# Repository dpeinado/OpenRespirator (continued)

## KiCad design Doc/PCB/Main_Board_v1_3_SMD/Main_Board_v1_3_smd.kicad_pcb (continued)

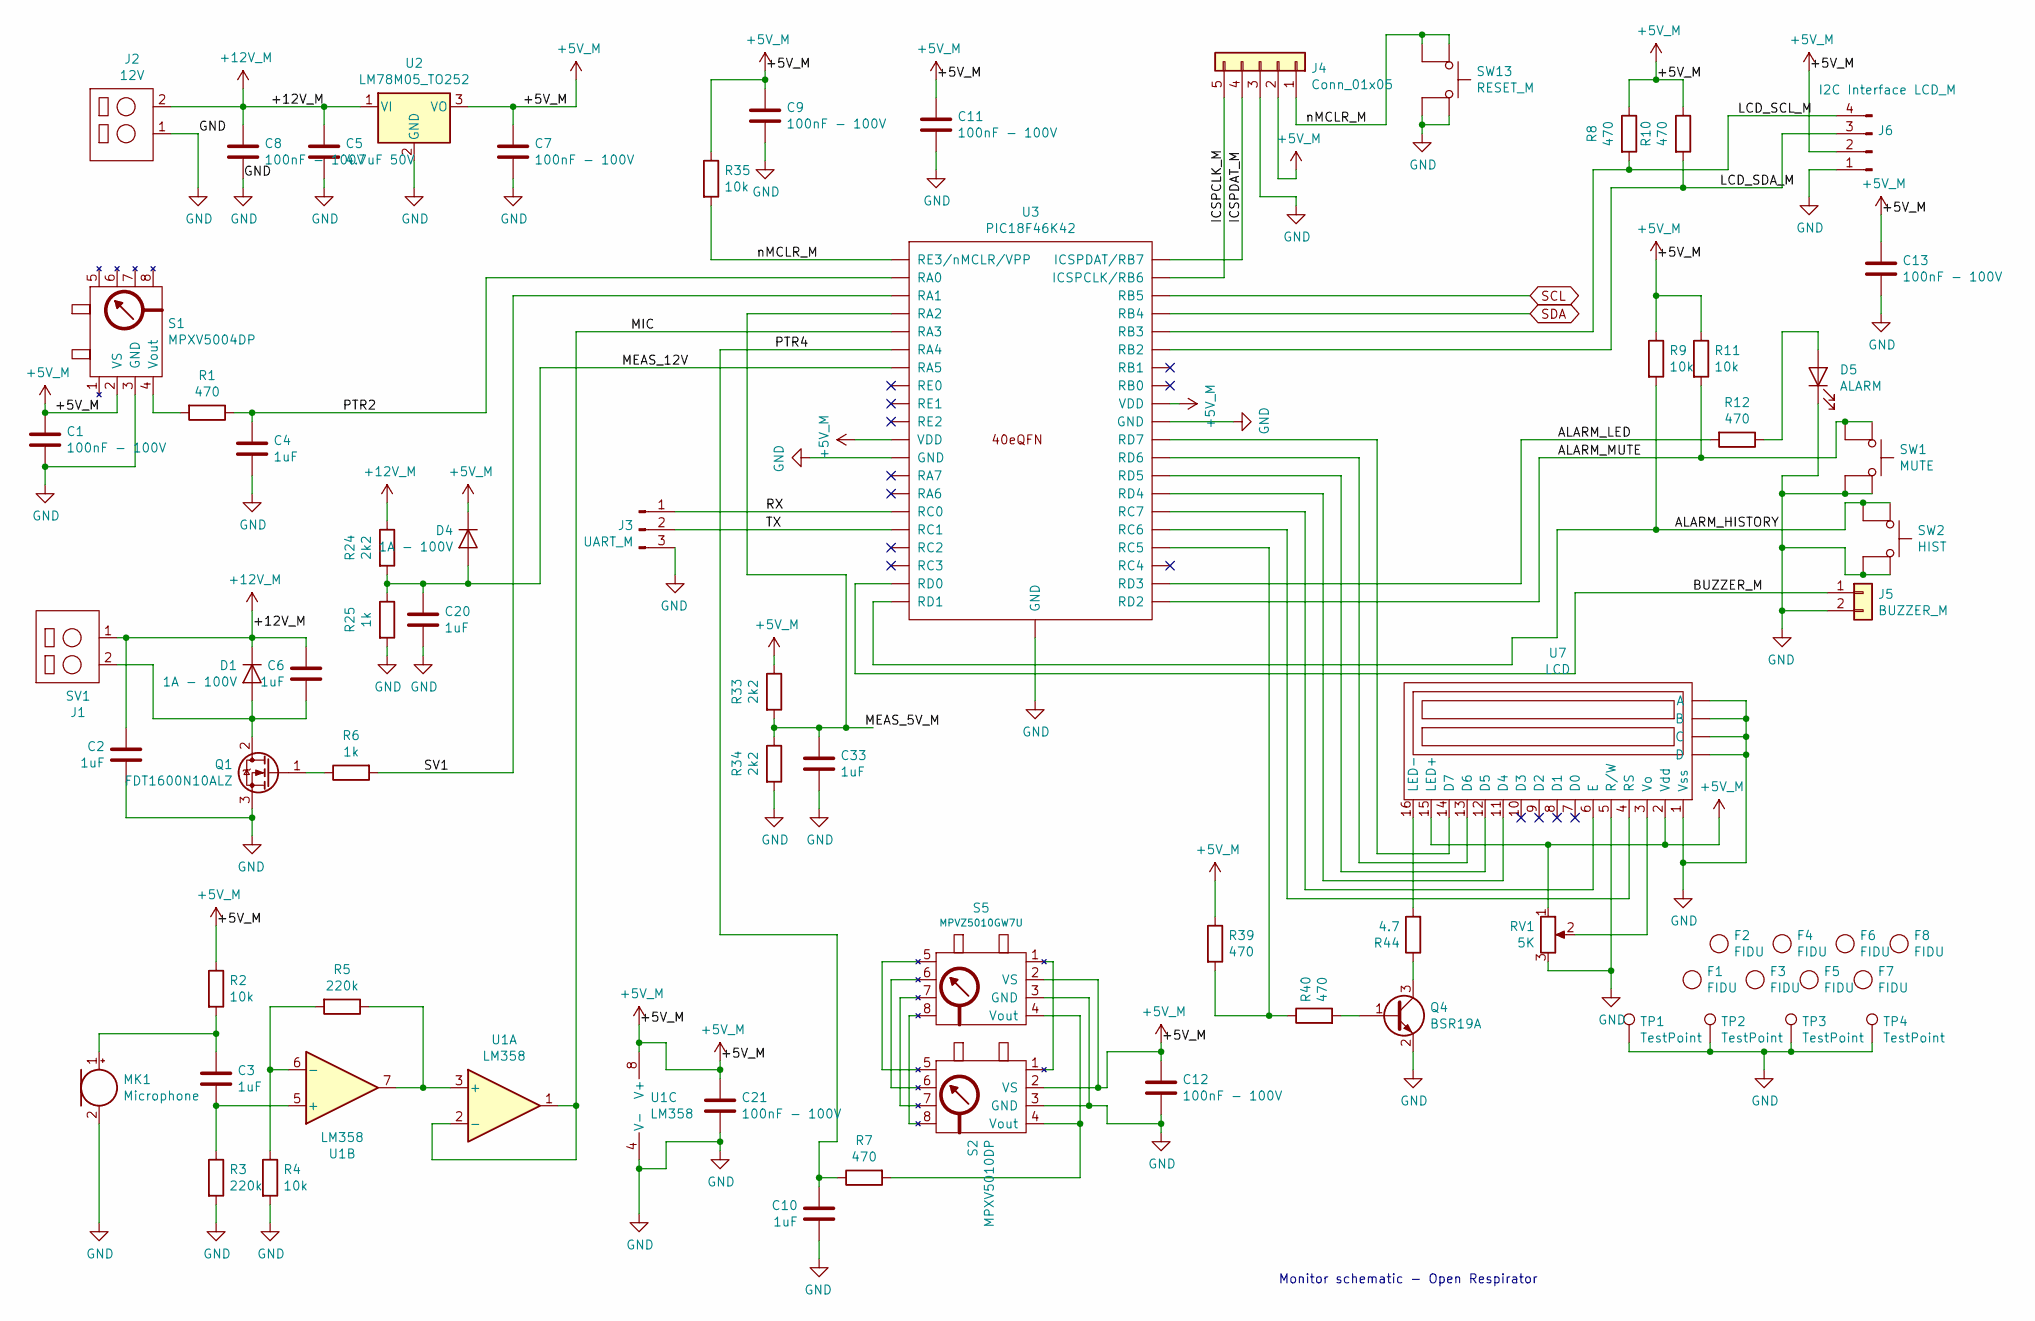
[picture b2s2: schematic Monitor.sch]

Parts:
C1, C7, C8, C9, C11, C12, C13, C21: 100nF - 100V; C_1206_3216Metric_Pad1.42x1.75mm_HandSolder
C2, C3, C4, C6, C10, C20, C33: 1uF; C_1206_3216Metric_Pad1.42x1.75mm_HandSolder
C5: 4.7uF 50V; CP_Radial_D5.0mm_P2.00mm
D1, D4: 1A - 100V; D_SMA-SMB_Universal_Handsoldering
D5: ALARM; LED_D3.0mm
F1, F2, F3, F4, F5, F6, F7, F8: FIDU; FIDUCIAL_TEST_PCB_1C
J1: SV1; PinHeader_1x02_Screwless_3.5mm
J2: 12V; PinHeader_1x02_Screwless_3.5mm
J3: UART_M; PinHeader_1x03_P2.54mm_Vertical
J4: Conn_01x05; PinHeader_1x05_P2.54mm_Horizontal
J5: BUZZER_M; PH_2_pol
J6: I2C Interface LCD_M; PH_4_pol
MK1: Microphone; MIC
Q1: FDT1600N10ALZ; SOT-223-3_TabPin2
Q4: BSR19A; SOT-23
R1, R7, R8, R10, R12, R39, R40: 470; R_0603_1608Metric_Pad1.05x0.95mm_HandSolder
R2, R4, R9, R11, R35: 10k; R_0603_1608Metric_Pad1.05x0.95mm_HandSolder
R3, R5: 220k; R_0603_1608Metric_Pad1.05x0.95mm_HandSolder
R6, R25: 1k; R_0603_1608Metric_Pad1.05x0.95mm_HandSolder
R24, R33, R34: 2k2; R_0603_1608Metric_Pad1.05x0.95mm_HandSolder
R44: 4.7; R_0603_1608Metric_Pad1.05x0.95mm_HandSolder
RV1: 5K; Potentiometer_Vishay_TS53YJ_Vertical
S1: MPXV5004DP; 1351-01
S2: MPXV5010DP; 1351-01
S5: MPVZ5010GW7U; 1560-03
SW1: MUTE; SW_PUSH_6mm_H13mm
SW2: HIST; SW_PUSH_6mm_H13mm
SW13: RESET_M; SW_PUSH_6mm_H13mm
TP1, TP2, TP3, TP4: TestPoint; PCB_DRILL
U1: LM358; SOIC-8-1EP_3.9x4.9mm_P1.27mm_EP2.41x3.3mm
U2: LM78M05_TO252; TO-252-2
U3: PIC18F46K42; QFN-40-1EP_5x5mm_P0.4mm_EP3.6x3.6mm_MedThermalVias
U7: LCD; LCD_2x16

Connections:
+5V_M: C1.1, C7.1, C9.1, C11.1, C12.1, C13.1, C21.1, D4.1 (K), J4.2, J6.2, R2.1, R8.1, R9.1, R10.1, R11.1, R33.1, R35.1, R39.1, RV1.1, S1.2 (VS), S2.2 (VS), S5.2 (VS), U1.8 (V+), U2.3 (VO), U3.7 (VDD), U3.26 (VDD), U7.2 (Vdd), U7.15 (LED+)
+12V_M: C2.1, C5.1, C6.1, C8.1, D1.1 (K), J1.1, J2.2, R24.1, U2.1 (VI)
/Monitor/ALARM_HISTORY: R9.2, SW2.1, U3.35 (RD1)
/Monitor/ALARM_LED: R12.2, U3.37 (RD3)
/Monitor/ALARM_MUTE: R11.2, SW1.1, U3.36 (RD2)
/Monitor/BUZZER_M: J5.1, U3.34 (RD0)
/Monitor/ICSPCLK_M: J4.5, U3.14 (ICSPCLK/RB6)
/Monitor/ICSPDAT_M: J4.4, U3.15 (ICSPDAT/RB7)
/Monitor/LCD_SCL_M: J6.4, R8.2, U3.11 (RB3)
/Monitor/LCD_SDA_M: J6.3, R10.2, U3.10 (RB2)
/Monitor/MEAS_5V_M: C33.1, R33.2, R34.1, U3.19 (RA2)
/Monitor/MEAS_12V: C20.1, D4.2 (A), R24.2, R25.1, U3.22 (RA5)
/Monitor/MIC: U1.1, U1.2 (-), U3.20 (RA3)
/Monitor/PTR2: C4.1, R1.1, U3.17 (RA0)
/Monitor/PTR4: C10.1, R7.1, U3.21 (RA4)
/Monitor/RX: J3.1, U3.30 (RC0)
/Monitor/SV1: R6.2, U3.18 (RA1)
/Monitor/TX: J3.2, U3.31 (RC1)
/Monitor/nMCLR_M: J4.1, R35.2, SW13.1, U3.16 (RE3/nMCLR/VPP)
GND: C1.2, C2.2, C4.2, C5.2, C7.2, C8.2, C9.2, C10.2, C11.2, C12.2, C13.2, C20.2, C21.2, C33.2, D5.1 (K), J2.1, J3.3, J4.3, J5.2, J6.1, MK1.2 (-), Q1.3 (S), Q4.2 (E), R3.2, R4.2, R25.2, R34.2, RV1.3, S1.3 (GND), S2.3 (GND), S5.3 (GND), SW1.2, SW2.2, SW13.2, TP1.1, TP2.1, TP3.1, TP4.1, U1.4 (V-), U2.2 (GND), U3.6 (GND), U3.27 (GND), U3.41 (GND), U7.1 (Vss), U7.5 (R/W), U7.~ (A); also elsewhere on the board
unnamed: C3.1, MK1.1 (+), R2.2
unnamed: C3.2, R3.1, U1.5 (+)
unnamed: C6.2, D1.2 (A), J1.2, Q1.2 (D)
unnamed: D5.2 (A), R12.1
unnamed: Q1.1 (G), R6.1
unnamed: Q4.1 (B), R40.2
unnamed: Q4.3 (C), R44.1
unnamed: R1.2, S1.4 (Vout)
unnamed: R4.1, R5.2, U1.6 (-)
unnamed: R5.1, U1.3 (+), U1.7
unnamed: R7.2, S2.4 (Vout), S5.4 (Vout)
unnamed: R39.2, R40.1, U3.39 (RC5)
unnamed: R44.2, U7.16 (LED-)
unnamed: RV1.2, U7.3 (Vo)
unnamed: S2.1, S5.1
unnamed: S2.5, S5.5
unnamed: S2.6, S5.6
unnamed: S2.7, S5.7
unnamed: S2.8, S5.8
unnamed: U3.1 (RC7), U7.6 (E)
unnamed: U3.2 (RD4), U7.11 (D4)
unnamed: U3.3 (RD5), U7.12 (D5)
unnamed: U3.4 (RD6), U7.13 (D6)
unnamed: U3.5 (RD7), U7.14 (D7)
unnamed: U3.40 (RC6), U7.4 (RS)
SCL: U3.13 (RB5); also elsewhere on the board
SDA: U3.12 (RB4); also elsewhere on the board

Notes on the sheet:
Monitor schematic - Open Respirator

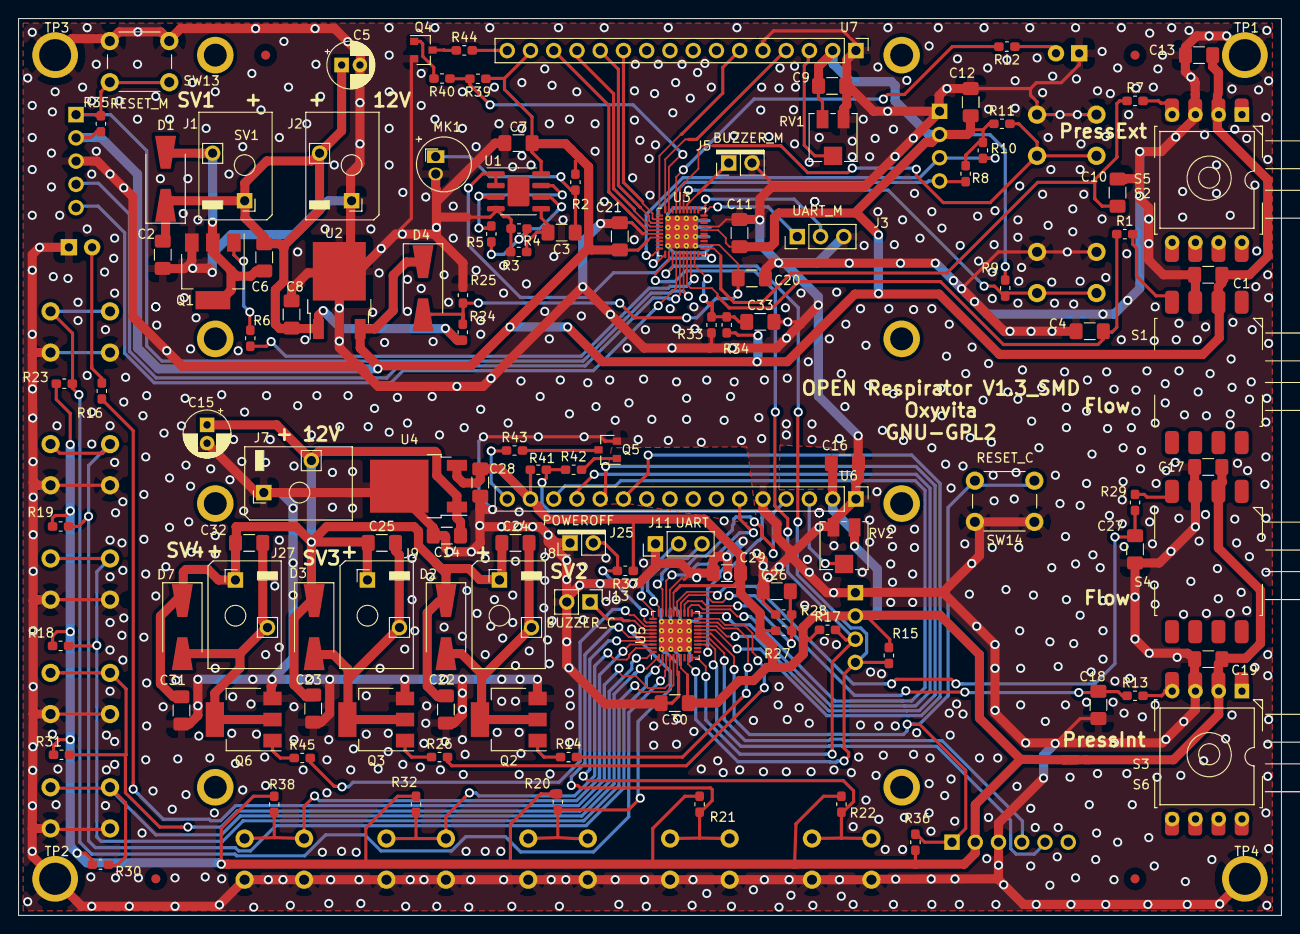
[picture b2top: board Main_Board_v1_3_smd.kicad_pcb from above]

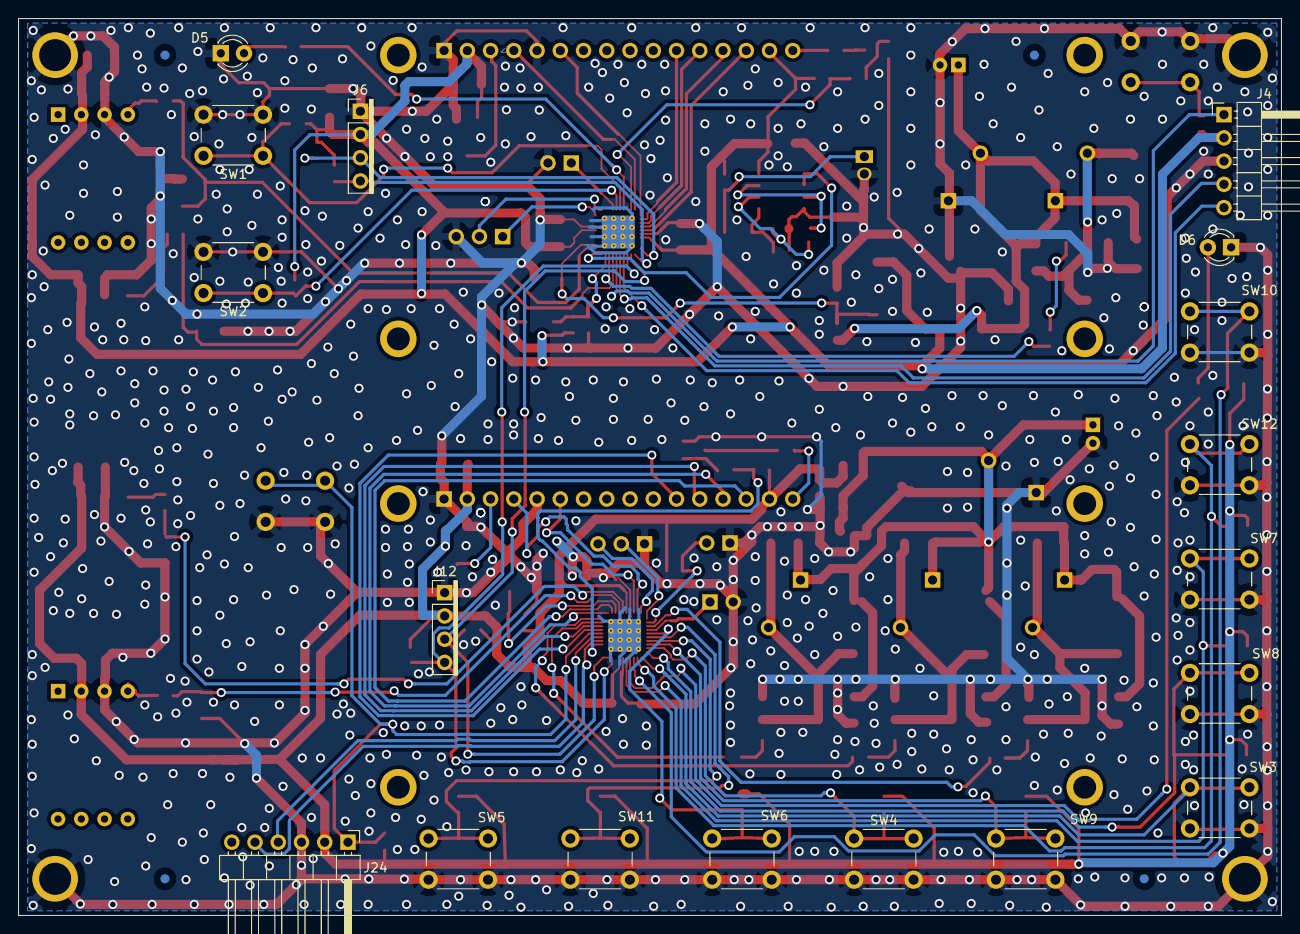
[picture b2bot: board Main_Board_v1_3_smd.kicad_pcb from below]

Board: 2 copper layers, 138.0 x 98.0 mm, 148 parts (22 on the bottom side), 98 nets.

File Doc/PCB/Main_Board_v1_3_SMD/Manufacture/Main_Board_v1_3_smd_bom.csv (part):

"Source:","/Users/carlospardo/MPLABXProjects/OpenRespirator/Doc/PCB/Main_Board_v1_3_SMD/Main_Board_v1_3_smd.sch"
"Date:","Wednesday, 08 July 2020 at 15:33:49"
"Tool:","Eeschema (5.1.5-0-10_14)"
"Component Count:","144"
"Ref","Value","Footprint","Datasheet","Manufacturer","Vendor"
"C1","100nF - 100V","Capacitor_SMD:C_1206_3216Metric_Pad1.42x1.75mm_HandSolder","https://es.rs-online.com/web/p/mlccs-condensadores-ceramicos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","",""
"C2","1uF","Capacitor_SMD:C_1206_3216Metric_Pad1.42x1.75mm_HandSolder","Capacitor_SMD:C_1206_3216Metric_Pad1.42x1.75mm_HandSolder","",""
"C3","1uF","Capacitor_SMD:C_1206_3216Metric_Pad1.42x1.75mm_HandSolder","Capacitor_SMD:C_1206_3216Metric_Pad1.42x1.75mm_HandSolder","",""
"C4","1uF","Capacitor_SMD:C_1206_3216Metric_Pad1.42x1.75mm_HandSolder","Capacitor_SMD:C_1206_3216Metric_Pad1.42x1.75mm_HandSolder","",""
"C5","4.7uF 50V","Capacitor_THT:CP_Radial_D5.0mm_P2.00mm","https://es.rs-online.com/web/p/condensadores-de-aluminio/1701286/","",""
"C6","1uF","Capacitor_SMD:C_1206_3216Metric_Pad1.42x1.75mm_HandSolder","Capacitor_SMD:C_1206_3216Metric_Pad1.42x1.75mm_HandSolder","",""
"C7","100nF - 100V","Capacitor_SMD:C_1206_3216Metric_Pad1.42x1.75mm_HandSolder","https://es.rs-online.com/web/p/mlccs-condensadores-ceramicos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","",""
"C8","100nF - 100V","Capacitor_SMD:C_1206_3216Metric_Pad1.42x1.75mm_HandSolder","https://es.rs-online.com/web/p/mlccs-condensadores-ceramicos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","",""
"C9","100nF - 100V","Capacitor_SMD:C_1206_3216Metric_Pad1.42x1.75mm_HandSolder","https://es.rs-online.com/web/p/mlccs-condensadores-ceramicos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","",""
"C10","1uF","Capacitor_SMD:C_1206_3216Metric_Pad1.42x1.75mm_HandSolder","Capacitor_SMD:C_1206_3216Metric_Pad1.42x1.75mm_HandSolder","",""
"C11","100nF - 100V","Capacitor_SMD:C_1206_3216Metric_Pad1.42x1.75mm_HandSolder","https://es.rs-online.com/web/p/mlccs-condensadores-ceramicos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","",""
"C12","100nF - 100V","Capacitor_SMD:C_1206_3216Metric_Pad1.42x1.75mm_HandSolder","https://es.rs-online.com/web/p/mlccs-condensadores-ceramicos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","",""
"C13","100nF - 100V","Capacitor_SMD:C_1206_3216Metric_Pad1.42x1.75mm_HandSolder","https://es.rs-online.com/web/p/mlccs-condensadores-ceramicos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","",""
"C14","100nF - 100V","Capacitor_SMD:C_1206_3216Metric_Pad1.42x1.75mm_HandSolder","https://es.rs-online.com/web/p/mlccs-condensadores-ceramicos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","",""
"C15","4.7uF 50V","Capacitor_THT:CP_Radial_D5.0mm_P2.00mm","https://es.rs-online.com/web/p/condensadores-de-aluminio/1701286/","",""
"C16","100nF - 100V","Capacitor_SMD:C_1206_3216Metric_Pad1.42x1.75mm_HandSolder","https://es.rs-online.com/web/p/mlccs-condensadores-ceramicos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","",""
"C17","100nF - 100V","Capacitor_SMD:C_1206_3216Metric_Pad1.42x1.75mm_HandSolder","https://es.rs-online.com/web/p/mlccs-condensadores-ceramicos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","",""
"C18","1uF","Capacitor_SMD:C_1206_3216Metric_Pad1.42x1.75mm_HandSolder","Capacitor_SMD:C_1206_3216Metric_Pad1.42x1.75mm_HandSolder","",""
"C19","100nF - 100V","Capacitor_SMD:C_1206_3216Metric_Pad1.42x1.75mm_HandSolder","https://es.rs-online.com/web/p/mlccs-condensadores-ceramicos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","",""
"C20","1uF","Capacitor_SMD:C_1206_3216Metric_Pad1.42x1.75mm_HandSolder","Capacitor_SMD:C_1206_3216Metric_Pad1.42x1.75mm_HandSolder","",""
"C21","100nF - 100V","Capacitor_SMD:C_1206_3216Metric_Pad1.42x1.75mm_HandSolder","https://es.rs-online.com/web/p/mlccs-condensadores-ceramicos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","",""
"C22","1uF","Capacitor_SMD:C_1206_3216Metric_Pad1.42x1.75mm_HandSolder","Capacitor_SMD:C_1206_3216Metric_Pad1.42x1.75mm_HandSolder","",""
"C23","1uF","Capacitor_SMD:C_1206_3216Metric_Pad1.42x1.75mm_HandSolder","Capacitor_SMD:C_1206_3216Metric_Pad1.42x1.75mm_HandSolder","",""
"C24","1uF","Capacitor_SMD:C_1206_3216Metric_Pad1.42x1.75mm_HandSolder","Capacitor_SMD:C_1206_3216Metric_Pad1.42x1.75mm_HandSolder","",""
"C25","1uF","Capacitor_SMD:C_1206_3216Metric_Pad1.42x1.75mm_HandSolder","Capacitor_SMD:C_1206_3216Metric_Pad1.42x1.75mm_HandSolder","",""
"C26","1uF","Capacitor_SMD:C_1206_3216Metric_Pad1.42x1.75mm_HandSolder","Capacitor_SMD:C_1206_3216Metric_Pad1.42x1.75mm_HandSolder","",""
"C27","1uF","Capacitor_SMD:C_1206_3216Metric_Pad1.42x1.75mm_HandSolder","Capacitor_SMD:C_1206_3216Metric_Pad1.42x1.75mm_HandSolder","",""
"C28","100nF - 100V","Capacitor_SMD:C_1206_3216Metric_Pad1.42x1.75mm_HandSolder","https://es.rs-online.com/web/p/mlccs-condensadores-ceramicos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","",""
"C29","100nF - 100V","Capacitor_SMD:C_1206_3216Metric_Pad1.42x1.75mm_HandSolder","https://es.rs-online.com/web/p/mlccs-condensadores-ceramicos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","",""
"C30","100nF - 100V","Capacitor_SMD:C_1206_3216Metric_Pad1.42x1.75mm_HandSolder","https://es.rs-online.com/web/p/mlccs-condensadores-ceramicos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","",""
"C31","1uF","Capacitor_SMD:C_1206_3216Metric_Pad1.42x1.75mm_HandSolder","Capacitor_SMD:C_1206_3216Metric_Pad1.42x1.75mm_HandSolder","",""
"C32","1uF","Capacitor_SMD:C_1206_3216Metric_Pad1.42x1.75mm_HandSolder","Capacitor_SMD:C_1206_3216Metric_Pad1.42x1.75mm_HandSolder","",""
"C33","1uF","Capacitor_SMD:C_1206_3216Metric_Pad1.42x1.75mm_HandSolder","Capacitor_SMD:C_1206_3216Metric_Pad1.42x1.75mm_HandSolder","",""
"D1","1A - 100V","Diode_SMD:D_SMA-SMB_Universal_Handsoldering","https://es.rs-online.com/web/p/diodo-de-conmutacion/1221183/","",""
"D2","1A - 100V","Diode_SMD:D_SMA-SMB_Universal_Handsoldering","https://es.rs-online.com/web/p/diodo-de-conmutacion/1221183/","",""
"D3","1A - 100V","Diode_SMD:D_SMA-SMB_Universal_Handsoldering","https://es.rs-online.com/web/p/diodo-de-conmutacion/1221183/","",""
"D4","1A - 100V","Diode_SMD:D_SMA-SMB_Universal_Handsoldering","https://es.rs-online.com/web/p/diodo-de-conmutacion/1221183/","",""
"D5","ALARM","LED_THT:LED_D3.0mm","~","",""
"D6","BREATH","LED_THT:LED_D3.0mm","~","",""
"D7","1A - 100V","Diode_SMD:D_SMA-SMB_Universal_Handsoldering","https://es.rs-online.com/web/p/diodo-de-conmutacion/1221183/","",""
"F1","FIDU","Ventilator:FIDUCIAL_TEST_PCB_1C","","",""
"F2","FIDU","Ventilator:FIDUCIAL_TEST_PCB_1C","","",""
"F3","FIDU","Ventilator:FIDUCIAL_TEST_PCB_1C","","",""
"F4","FIDU","Ventilator:FIDUCIAL_TEST_PCB_1C","","",""
"F5","FIDU","Ventilator:FIDUCIAL_TEST_PCB_1C","","",""
"F6","FIDU","Ventilator:FIDUCIAL_TEST_PCB_1C","","",""
"F7","FIDU","Ventilator:FIDUCIAL_TEST_PCB_1C","","",""
"F8","FIDU","Ventilator:FIDUCIAL_TEST_PCB_1C","","",""
"J1","SV1","Ventilator:PinHeader_1x02_Screwless_3.5mm","https://es.rs-online.com/web/p/bloques-terminales-para-pcb/1232052/","",""
"J2","12V","Ventilator:PinHeader_1x02_Screwless_3.5mm","https://es.rs-online.com/web/p/bloques-terminales-para-pcb/1232052/","",""
"J3","UART_M","Connector_PinHeader_2.54mm:PinHeader_1x03_P2.54mm_Vertical","~","",""
"J4","Conn_01x05","Connector_PinHeader_2.54mm:PinHeader_1x05_P2.54mm_Horizontal","~","",""
"J5","BUZZER_M","Ventilator:PH_2_pol","https://es.rs-online.com/web/p/componentes-de-piezo-buzzer/6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","",""
"J6","I2C Interface LCD_M","Ventilator:PH_4_pol","~","",""
"J7","12V","Ventilator:PinHeader_1x02_Screwless_3.5mm","https://es.rs-online.com/web/p/bloques-terminales-para-pcb/1232052/","",""
"J8","SV2","Ventilator:PinHeader_1x02_Screwless_3.5mm","https://es.rs-online.com/web/p/bloques-terminales-para-pcb/1232052/","",""
"J9","SV3","Ventilator:PinHeader_1x02_Screwless_3.5mm","https://es.rs-online.com/web/p/bloques-terminales-para-pcb/1232052/","",""
"J11","UART","Connector_PinHeader_2.54mm:PinHeader_1x03_P2.54mm_Vertical","~","",""
"J12","I2C Interface LCD_C","Ventilator:PH_4_pol","~","",""
"J13","BUZZER_C","Connector_PinHeader_2.54mm:PinHeader_1x02_P2.54mm_Vertical","https://es.rs-online.com/web/p/componentes-de-piezo-buzzer/6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","",""
"J24","Conn_01x06","Connector_PinHeader_2.54mm:PinHeader_1x06_P2.54mm_Horizontal","~","",""
"J25","POWEROFF","Ventilator:PH_2_pol","","",""
"J27","SV4","Ventilator:PinHeader_1x02_Screwless_3.5mm","https://es.rs-online.com/web/p/bloques-terminales-para-pcb/1232052/","",""
"MK1","Microphone","Ventilator:MIC","https://es.rs-online.com/web/p/componentes-de-microfono-para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","",""
"Q1","FDT1600N10ALZ","Package_TO_SOT_SMD:SOT-223-3_TabPin2","https://es.rs-online.com/web/p/mosfet/1662305/","",""
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
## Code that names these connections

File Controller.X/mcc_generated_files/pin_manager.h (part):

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// get/set IO_RA0 aliases
#define IO_RA0_TRIS                 TRISAbits.TRISA0
#define IO_RA0_LAT                  LATAbits.LATA0
#define IO_RA0_PORT                 PORTAbits.RA0
#define IO_RA0_WPU                  WPUAbits.WPUA0
#define IO_RA0_OD                   ODCONAbits.ODCA0
#define IO_RA0_ANS                  ANSELAbits.ANSELA0
#define IO_RA0_SetHigh()            do { LATAbits.LATA0 = 1; } while(0)
#define IO_RA0_SetLow()             do { LATAbits.LATA0 = 0; } while(0)
#define IO_RA0_Toggle()             do { LATAbits.LATA0 = ~LATAbits.LATA0; } while(0)
#define IO_RA0_GetValue()           PORTAbits.RA0
#define IO_RA0_SetDigitalInput()    do { TRISAbits.TRISA0 = 1; } while(0)
#define IO_RA0_SetDigitalOutput()   do { TRISAbits.TRISA0 = 0; } while(0)
#define IO_RA0_SetPullup()          do { WPUAbits.WPUA0 = 1; } while(0)
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// get/set IO_RA1 aliases
#define IO_RA1_TRIS                 TRISAbits.TRISA1
#define IO_RA1_LAT                  LATAbits.LATA1
#define IO_RA1_PORT                 PORTAbits.RA1
#define IO_RA1_WPU                  WPUAbits.WPUA1
#define IO_RA1_OD                   ODCONAbits.ODCA1
#define IO_RA1_ANS                  ANSELAbits.ANSELA1
#define IO_RA1_SetHigh()            do { LATAbits.LATA1 = 1; } while(0)
#define IO_RA1_SetLow()             do { LATAbits.LATA1 = 0; } while(0)
#define IO_RA1_Toggle()             do { LATAbits.LATA1 = ~LATAbits.LATA1; } while(0)
#define IO_RA1_GetValue()           PORTAbits.RA1
#define IO_RA1_SetDigitalInput()    do { TRISAbits.TRISA1 = 1; } while(0)
#define IO_RA1_SetDigitalOutput()   do { TRISAbits.TRISA1 = 0; } while(0)
#define IO_RA1_SetPullup()          do { WPUAbits.WPUA1 = 1; } while(0)
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// get/set IO_RA2 aliases
#define IO_RA2_TRIS                 TRISAbits.TRISA2
#define IO_RA2_LAT                  LATAbits.LATA2
#define IO_RA2_PORT                 PORTAbits.RA2
#define IO_RA2_WPU                  WPUAbits.WPUA2
#define IO_RA2_OD                   ODCONAbits.ODCA2
#define IO_RA2_ANS                  ANSELAbits.ANSELA2
#define IO_RA2_SetHigh()            do { LATAbits.LATA2 = 1; } while(0)
#define IO_RA2_SetLow()             do { LATAbits.LATA2 = 0; } while(0)
#define IO_RA2_Toggle()             do { LATAbits.LATA2 = ~LATAbits.LATA2; } while(0)
#define IO_RA2_GetValue()           PORTAbits.RA2
#define IO_RA2_SetDigitalInput()    do { TRISAbits.TRISA2 = 1; } while(0)
#define IO_RA2_SetDigitalOutput()   do { TRISAbits.TRISA2 = 0; } while(0)
#define IO_RA2_SetPullup()          do { WPUAbits.WPUA2 = 1; } while(0)
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// get/set IO_RA3 aliases
#define IO_RA3_TRIS                 TRISAbits.TRISA3
#define IO_RA3_LAT                  LATAbits.LATA3
#define IO_RA3_PORT                 PORTAbits.RA3
#define IO_RA3_WPU                  WPUAbits.WPUA3
#define IO_RA3_OD                   ODCONAbits.ODCA3
#define IO_RA3_ANS                  ANSELAbits.ANSELA3
#define IO_RA3_SetHigh()            do { LATAbits.LATA3 = 1; } while(0)
#define IO_RA3_SetLow()             do { LATAbits.LATA3 = 0; } while(0)
#define IO_RA3_Toggle()             do { LATAbits.LATA3 = ~LATAbits.LATA3; } while(0)
#define IO_RA3_GetValue()           PORTAbits.RA3
#define IO_RA3_SetDigitalInput()    do { TRISAbits.TRISA3 = 1; } while(0)
#define IO_RA3_SetDigitalOutput()   do { TRISAbits.TRISA3 = 0; } while(0)
#define IO_RA3_SetPullup()          do { WPUAbits.WPUA3 = 1; } while(0)
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// get/set IO_RA4 aliases
#define IO_RA4_TRIS                 TRISAbits.TRISA4
#define IO_RA4_LAT                  LATAbits.LATA4
#define IO_RA4_PORT                 PORTAbits.RA4
#define IO_RA4_WPU                  WPUAbits.WPUA4
#define IO_RA4_OD                   ODCONAbits.ODCA4
#define IO_RA4_ANS                  ANSELAbits.ANSELA4
#define IO_RA4_SetHigh()            do { LATAbits.LATA4 = 1; } while(0)
#define IO_RA4_SetLow()             do { LATAbits.LATA4 = 0; } while(0)
#define IO_RA4_Toggle()             do { LATAbits.LATA4 = ~LATAbits.LATA4; } while(0)
#define IO_RA4_GetValue()           PORTAbits.RA4
#define IO_RA4_SetDigitalInput()    do { TRISAbits.TRISA4 = 1; } while(0)
#define IO_RA4_SetDigitalOutput()   do { TRISAbits.TRISA4 = 0; } while(0)
#define IO_RA4_SetPullup()          do { WPUAbits.WPUA4 = 1; } while(0)
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// get/set IO_RA5 aliases
#define IO_RA5_TRIS                 TRISAbits.TRISA5
#define IO_RA5_LAT                  LATAbits.LATA5
#define IO_RA5_PORT                 PORTAbits.RA5
#define IO_RA5_WPU                  WPUAbits.WPUA5
#define IO_RA5_OD                   ODCONAbits.ODCA5
#define IO_RA5_ANS                  ANSELAbits.ANSELA5
#define IO_RA5_SetHigh()            do { LATAbits.LATA5 = 1; } while(0)
#define IO_RA5_SetLow()             do { LATAbits.LATA5 = 0; } while(0)
#define IO_RA5_Toggle()             do { LATAbits.LATA5 = ~LATAbits.LATA5; } while(0)
#define IO_RA5_GetValue()           PORTAbits.RA5
#define IO_RA5_SetDigitalInput()    do { TRISAbits.TRISA5 = 1; } while(0)
#define IO_RA5_SetDigitalOutput()   do { TRISAbits.TRISA5 = 0; } while(0)
#define IO_RA5_SetPullup()          do { WPUAbits.WPUA5 = 1; } while(0)
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// get/set IO_RA6 aliases
#define IO_RA6_TRIS                 TRISAbits.TRISA6
#define IO_RA6_LAT                  LATAbits.LATA6
#define IO_RA6_PORT                 PORTAbits.RA6
#define IO_RA6_WPU                  WPUAbits.WPUA6
#define IO_RA6_OD                   ODCONAbits.ODCA6
#define IO_RA6_ANS                  ANSELAbits.ANSELA6
#define IO_RA6_SetHigh()            do { LATAbits.LATA6 = 1; } while(0)
#define IO_RA6_SetLow()             do { LATAbits.LATA6 = 0; } while(0)
#define IO_RA6_Toggle()             do { LATAbits.LATA6 = ~LATAbits.LATA6; } while(0)
#define IO_RA6_GetValue()           PORTAbits.RA6
#define IO_RA6_SetDigitalInput()    do { TRISAbits.TRISA6 = 1; } while(0)
#define IO_RA6_SetDigitalOutput()   do { TRISAbits.TRISA6 = 0; } while(0)
#define IO_RA6_SetPullup()          do { WPUAbits.WPUA6 = 1; } while(0)
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// get/set IO_RA7 aliases
#define IO_RA7_TRIS                 TRISAbits.TRISA7
#define IO_RA7_LAT                  LATAbits.LATA7
#define IO_RA7_PORT                 PORTAbits.RA7
#define IO_RA7_WPU                  WPUAbits.WPUA7
#define IO_RA7_OD                   ODCONAbits.ODCA7
#define IO_RA7_ANS                  ANSELAbits.ANSELA7
#define IO_RA7_SetHigh()            do { LATAbits.LATA7 = 1; } while(0)
#define IO_RA7_SetLow()             do { LATAbits.LATA7 = 0; } while(0)
#define IO_RA7_Toggle()             do { LATAbits.LATA7 = ~LATAbits.LATA7; } while(0)
#define IO_RA7_GetValue()           PORTAbits.RA7
#define IO_RA7_SetDigitalInput()    do { TRISAbits.TRISA7 = 1; } while(0)
#define IO_RA7_SetDigitalOutput()   do { TRISAbits.TRISA7 = 0; } while(0)
#define IO_RA7_SetPullup()          do { WPUAbits.WPUA7 = 1; } while(0)
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#define RB1_SetHigh()            do { LATBbits.LATB1 = 1; } while(0)
#define RB1_SetLow()             do { LATBbits.LATB1 = 0; } while(0)
#define RB1_Toggle()             do { LATBbits.LATB1 = ~LATBbits.LATB1; } while(0)
#define RB1_GetValue()              PORTBbits.RB1
#define RB1_SetDigitalInput()    do { TRISBbits.TRISB1 = 1; } while(0)
#define RB1_SetDigitalOutput()   do { TRISBbits.TRISB1 = 0; } while(0)
#define RB1_SetPullup()             do { WPUBbits.WPUB1 = 1; } while(0)
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#define RB2_SetHigh()            do { LATBbits.LATB2 = 1; } while(0)
#define RB2_SetLow()             do { LATBbits.LATB2 = 0; } while(0)
#define RB2_Toggle()             do { LATBbits.LATB2 = ~LATBbits.LATB2; } while(0)
#define RB2_GetValue()              PORTBbits.RB2
#define RB2_SetDigitalInput()    do { TRISBbits.TRISB2 = 1; } while(0)
#define RB2_SetDigitalOutput()   do { TRISBbits.TRISB2 = 0; } while(0)
#define RB2_SetPullup()             do { WPUBbits.WPUB2 = 1; } while(0)
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// get/set IO_RB3 aliases
#define IO_RB3_TRIS                 TRISBbits.TRISB3
#define IO_RB3_LAT                  LATBbits.LATB3
#define IO_RB3_PORT                 PORTBbits.RB3
#define IO_RB3_WPU                  WPUBbits.WPUB3
#define IO_RB3_OD                   ODCONBbits.ODCB3
#define IO_RB3_ANS                  ANSELBbits.ANSELB3
#define IO_RB3_SetHigh()            do { LATBbits.LATB3 = 1; } while(0)
#define IO_RB3_SetLow()             do { LATBbits.LATB3 = 0; } while(0)
#define IO_RB3_Toggle()             do { LATBbits.LATB3 = ~LATBbits.LATB3; } while(0)
#define IO_RB3_GetValue()           PORTBbits.RB3
#define IO_RB3_SetDigitalInput()    do { TRISBbits.TRISB3 = 1; } while(0)
#define IO_RB3_SetDigitalOutput()   do { TRISBbits.TRISB3 = 0; } while(0)
#define IO_RB3_SetPullup()          do { WPUBbits.WPUB3 = 1; } while(0)
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// get/set IO_RB4 aliases
#define IO_RB4_TRIS                 TRISBbits.TRISB4
#define IO_RB4_LAT                  LATBbits.LATB4
#define IO_RB4_PORT                 PORTBbits.RB4
#define IO_RB4_WPU                  WPUBbits.WPUB4
#define IO_RB4_OD                   ODCONBbits.ODCB4
#define IO_RB4_ANS                  ANSELBbits.ANSELB4
#define IO_RB4_SetHigh()            do { LATBbits.LATB4 = 1; } while(0)
#define IO_RB4_SetLow()             do { LATBbits.LATB4 = 0; } while(0)
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
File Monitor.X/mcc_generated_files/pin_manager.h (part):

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// get/set PRSV aliases
#define PRSV_TRIS                 TRISAbits.TRISA0
#define PRSV_LAT                  LATAbits.LATA0
#define PRSV_PORT                 PORTAbits.RA0
#define PRSV_WPU                  WPUAbits.WPUA0
#define PRSV_OD                   ODCONAbits.ODCA0
#define PRSV_ANS                  ANSELAbits.ANSELA0
#define PRSV_SetHigh()            do { LATAbits.LATA0 = 1; } while(0)
#define PRSV_SetLow()             do { LATAbits.LATA0 = 0; } while(0)
#define PRSV_Toggle()             do { LATAbits.LATA0 = ~LATAbits.LATA0; } while(0)
#define PRSV_GetValue()           PORTAbits.RA0
#define PRSV_SetDigitalInput()    do { TRISAbits.TRISA0 = 1; } while(0)
#define PRSV_SetDigitalOutput()   do { TRISAbits.TRISA0 = 0; } while(0)
#define PRSV_SetPullup()          do { WPUAbits.WPUA0 = 1; } while(0)
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// get/set VALVE aliases
#define VALVE_TRIS                 TRISAbits.TRISA1
#define VALVE_LAT                  LATAbits.LATA1
#define VALVE_PORT                 PORTAbits.RA1
#define VALVE_WPU                  WPUAbits.WPUA1
#define VALVE_OD                   ODCONAbits.ODCA1
#define VALVE_ANS                  ANSELAbits.ANSELA1
#define VALVE_SetHigh()            do { LATAbits.LATA1 = 1; } while(0)
#define VALVE_SetLow()             do { LATAbits.LATA1 = 0; } while(0)
#define VALVE_Toggle()             do { LATAbits.LATA1 = ~LATAbits.LATA1; } while(0)
#define VALVE_GetValue()           PORTAbits.RA1
#define VALVE_SetDigitalInput()    do { TRISAbits.TRISA1 = 1; } while(0)
#define VALVE_SetDigitalOutput()   do { TRISAbits.TRISA1 = 0; } while(0)
#define VALVE_SetPullup()          do { WPUAbits.WPUA1 = 1; } while(0)
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// get/set MEAS5 aliases
#define MEAS5_TRIS                 TRISAbits.TRISA2
#define MEAS5_LAT                  LATAbits.LATA2
#define MEAS5_PORT                 PORTAbits.RA2
#define MEAS5_WPU                  WPUAbits.WPUA2
#define MEAS5_OD                   ODCONAbits.ODCA2
#define MEAS5_ANS                  ANSELAbits.ANSELA2
#define MEAS5_SetHigh()            do { LATAbits.LATA2 = 1; } while(0)
#define MEAS5_SetLow()             do { LATAbits.LATA2 = 0; } while(0)
#define MEAS5_Toggle()             do { LATAbits.LATA2 = ~LATAbits.LATA2; } while(0)
#define MEAS5_GetValue()           PORTAbits.RA2
#define MEAS5_SetDigitalInput()    do { TRISAbits.TRISA2 = 1; } while(0)
#define MEAS5_SetDigitalOutput()   do { TRISAbits.TRISA2 = 0; } while(0)
#define MEAS5_SetPullup()          do { WPUAbits.WPUA2 = 1; } while(0)
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// get/set MIC aliases
#define MIC_TRIS                 TRISAbits.TRISA3
#define MIC_LAT                  LATAbits.LATA3
#define MIC_PORT                 PORTAbits.RA3
#define MIC_WPU                  WPUAbits.WPUA3
#define MIC_OD                   ODCONAbits.ODCA3
#define MIC_ANS                  ANSELAbits.ANSELA3
#define MIC_SetHigh()            do { LATAbits.LATA3 = 1; } while(0)
#define MIC_SetLow()             do { LATAbits.LATA3 = 0; } while(0)
#define MIC_Toggle()             do { LATAbits.LATA3 = ~LATAbits.LATA3; } while(0)
#define MIC_GetValue()           PORTAbits.RA3
#define MIC_SetDigitalInput()    do { TRISAbits.TRISA3 = 1; } while(0)
#define MIC_SetDigitalOutput()   do { TRISAbits.TRISA3 = 0; } while(0)
#define MIC_SetPullup()          do { WPUAbits.WPUA3 = 1; } while(0)
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// get/set PRS aliases
#define PRS_TRIS                 TRISAbits.TRISA4
#define PRS_LAT                  LATAbits.LATA4
#define PRS_PORT                 PORTAbits.RA4
#define PRS_WPU                  WPUAbits.WPUA4
#define PRS_OD                   ODCONAbits.ODCA4
#define PRS_ANS                  ANSELAbits.ANSELA4
#define PRS_SetHigh()            do { LATAbits.LATA4 = 1; } while(0)
#define PRS_SetLow()             do { LATAbits.LATA4 = 0; } while(0)
#define PRS_Toggle()             do { LATAbits.LATA4 = ~LATAbits.LATA4; } while(0)
#define PRS_GetValue()           PORTAbits.RA4
#define PRS_SetDigitalInput()    do { TRISAbits.TRISA4 = 1; } while(0)
#define PRS_SetDigitalOutput()   do { TRISAbits.TRISA4 = 0; } while(0)
#define PRS_SetPullup()          do { WPUAbits.WPUA4 = 1; } while(0)
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// get/set MEAS12 aliases
#define MEAS12_TRIS                 TRISAbits.TRISA5
#define MEAS12_LAT                  LATAbits.LATA5
#define MEAS12_PORT                 PORTAbits.RA5
#define MEAS12_WPU                  WPUAbits.WPUA5
#define MEAS12_OD                   ODCONAbits.ODCA5
#define MEAS12_ANS                  ANSELAbits.ANSELA5
#define MEAS12_SetHigh()            do { LATAbits.LATA5 = 1; } while(0)
#define MEAS12_SetLow()             do { LATAbits.LATA5 = 0; } while(0)
#define MEAS12_Toggle()             do { LATAbits.LATA5 = ~LATAbits.LATA5; } while(0)
#define MEAS12_GetValue()           PORTAbits.RA5
#define MEAS12_SetDigitalInput()    do { TRISAbits.TRISA5 = 1; } while(0)
#define MEAS12_SetDigitalOutput()   do { TRISAbits.TRISA5 = 0; } while(0)
#define MEAS12_SetPullup()          do { WPUAbits.WPUA5 = 1; } while(0)
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#define RB4_SetHigh()            do { LATBbits.LATB4 = 1; } while(0)
#define RB4_SetLow()             do { LATBbits.LATB4 = 0; } while(0)
#define RB4_Toggle()             do { LATBbits.LATB4 = ~LATBbits.LATB4; } while(0)
#define RB4_GetValue()              PORTBbits.RB4
#define RB4_SetDigitalInput()    do { TRISBbits.TRISB4 = 1; } while(0)
#define RB4_SetDigitalOutput()   do { TRISBbits.TRISB4 = 0; } while(0)
#define RB4_SetPullup()             do { WPUBbits.WPUB4 = 1; } while(0)
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#define RB5_SetHigh()            do { LATBbits.LATB5 = 1; } while(0)
#define RB5_SetLow()             do { LATBbits.LATB5 = 0; } while(0)
#define RB5_Toggle()             do { LATBbits.LATB5 = ~LATBbits.LATB5; } while(0)
#define RB5_GetValue()              PORTBbits.RB5
#define RB5_SetDigitalInput()    do { TRISBbits.TRISB5 = 1; } while(0)
#define RB5_SetDigitalOutput()   do { TRISBbits.TRISB5 = 0; } while(0)
#define RB5_SetPullup()             do { WPUBbits.WPUB5 = 1; } while(0)
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#define RC0_SetHigh()            do { LATCbits.LATC0 = 1; } while(0)
#define RC0_SetLow()             do { LATCbits.LATC0 = 0; } while(0)
#define RC0_Toggle()             do { LATCbits.LATC0 = ~LATCbits.LATC0; } while(0)
#define RC0_GetValue()              PORTCbits.RC0
#define RC0_SetDigitalInput()    do { TRISCbits.TRISC0 = 1; } while(0)
#define RC0_SetDigitalOutput()   do { TRISCbits.TRISC0 = 0; } while(0)
#define RC0_SetPullup()             do { WPUCbits.WPUC0 = 1; } while(0)
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#define RC1_SetHigh()            do { LATCbits.LATC1 = 1; } while(0)
#define RC1_SetLow()             do { LATCbits.LATC1 = 0; } while(0)
#define RC1_Toggle()             do { LATCbits.LATC1 = ~LATCbits.LATC1; } while(0)
#define RC1_GetValue()              PORTCbits.RC1
#define RC1_SetDigitalInput()    do { TRISCbits.TRISC1 = 1; } while(0)
#define RC1_SetDigitalOutput()   do { TRISCbits.TRISC1 = 0; } while(0)
#define RC1_SetPullup()             do { WPUCbits.WPUC1 = 1; } while(0)
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// get/set LLED aliases
#define LLED_TRIS                 TRISCbits.TRISC5
#define LLED_LAT                  LATCbits.LATC5
#define LLED_PORT                 PORTCbits.RC5
#define LLED_WPU                  WPUCbits.WPUC5
#define LLED_OD                   ODCONCbits.ODCC5
#define LLED_ANS                  ANSELCbits.ANSELC5
#define LLED_SetHigh()            do { LATCbits.LATC5 = 1; } while(0)
#define LLED_SetLow()             do { LATCbits.LATC5 = 0; } while(0)
#define LLED_Toggle()             do { LATCbits.LATC5 = ~LATCbits.LATC5; } while(0)
#define LLED_GetValue()           PORTCbits.RC5
#define LLED_SetDigitalInput()    do { TRISCbits.TRISC5 = 1; } while(0)
#define LLED_SetDigitalOutput()   do { TRISCbits.TRISC5 = 0; } while(0)
#define LLED_SetPullup()          do { WPUCbits.WPUC5 = 1; } while(0)
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// get/set RS aliases
#define RS_TRIS                 TRISCbits.TRISC6
#define RS_LAT                  LATCbits.LATC6
#define RS_PORT                 PORTCbits.RC6
#define RS_WPU                  WPUCbits.WPUC6
#define RS_OD                   ODCONCbits.ODCC6
#define RS_ANS                  ANSELCbits.ANSELC6
#define RS_SetHigh()            do { LATCbits.LATC6 = 1; } while(0)
#define RS_SetLow()             do { LATCbits.LATC6 = 0; } while(0)
#define RS_Toggle()             do { LATCbits.LATC6 = ~LATCbits.LATC6; } while(0)
#define RS_GetValue()           PORTCbits.RC6
#define RS_SetDigitalInput()    do { TRISCbits.TRISC6 = 1; } while(0)
#define RS_SetDigitalOutput()   do { TRISCbits.TRISC6 = 0; } while(0)
#define RS_SetPullup()          do { WPUCbits.WPUC6 = 1; } while(0)
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// get/set E aliases
#define E_TRIS                 TRISCbits.TRISC7
#define E_LAT                  LATCbits.LATC7
#define E_PORT                 PORTCbits.RC7
#define E_WPU                  WPUCbits.WPUC7
#define E_OD                   ODCONCbits.ODCC7
#define E_ANS                  ANSELCbits.ANSELC7
#define E_SetHigh()            do { LATCbits.LATC7 = 1; } while(0)
#define E_SetLow()             do { LATCbits.LATC7 = 0; } while(0)
#define E_Toggle()             do { LATCbits.LATC7 = ~LATCbits.LATC7; } while(0)
#define E_GetValue()           PORTCbits.RC7
#define E_SetDigitalInput()    do { TRISCbits.TRISC7 = 1; } while(0)
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
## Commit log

2020-04-02 Create License
    First License file.
    GNU
2020-04-02 First Commit Controller pinout defined. No Functionality
2020-04-03 Monitor Pin configuration. NO functionality
2020-04-03 Added pressure functions and first printf
2020-04-03 Added Documentation
    Added Sample program
2020-04-04 DOR: WIP, basic time function.
2020-04-04 DOR: WIP, basic adc capture function.
2020-04-04 Added display functionality
2020-04-04 Added first pictures
2020-04-04 Fixing compilation errors Added buttons
2020-04-04 DOR: WIP, basic functionality for respiration. Still to be debugged.
2020-04-04 Added Controller
2020-04-05 First Buzzer implementation More pictures
2020-04-05 Working Alarm in Buzzer
2020-04-05 DOR: Added 1/2 IIR filtering on ADC captures.
2020-04-05 Fixed pressure meassure
2020-04-05 First Alarm Implementation
2020-04-06 Alarms works
2020-04-07 Fixes in alarm Start of pressure monitor
2020-04-07 DOR: Added new pressure sensor. 5010.
2020-04-07 DOR: Added proper filtering and handling of ADC. Now three filtered versions of main pressure with 32ms, 64ms and 1s are generated. Simple first order IIR LPF. Moreover ADC has proper sampling settin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
2020-04-08 several updates
2020-04-08 DOR: WIP. Adjusted ADC for exact 1KHz sampling frequency with 3 sources, with room for a fourth (it would be interesting to monitor power supply to generate alarm).
2020-04-08 Added sampling filter. Slow and Fast
2020-04-09 DOR: WIP. Implemented valve actuation delay, and prediction on the pressure for compensating for the actuation delay.
2020-04-09 Increased baudrate of UART to 460800 and buffer to 64 bytes to reduce overhead of debug.
2020-04-09 DOR: Implemented another type of control for control of SV3 open, for better compensation of response.
2020-04-09 Buttons, and alarm working
2020-04-09 DOR: Refactoring, variable name changes. Added secondary control on IP for better precision. Also added hysteresis on the fixed-time opening of SV2 during the plateau to reduce overshoots, since even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
2020-04-10 Working version of Monitor
2020-04-10 DOR: integrated volume measurement. Pre-calibration with a 5l bottle.
2020-04-10 DOR: fixed bug during code optimization.
2020-04-10 DOR: change PI plateau measurement to take max value during first 60ms after valve close to avoid overshoot if circuit has losses.
2020-04-10 DOR: added breath detection.
2020-04-11 WIP, adding control and display.
2020-04-12 LCD 2 lines I2C working
2020-04-12 Update Readme with ToDo list
2020-04-12 Fix format
2020-04-12 LCD Working. New DOC
2020-04-12 Clean up images
2020-04-13 Added New DOC and Images. General Monitor update
2020-04-14 Added images and update doc. Monitor improved
2020-04-14 Added pressure alarms implementation
2020-04-16 New Monitor architecture. First demo working
2020-04-16 Added more I2C bits to Specification
2020-04-18 New Schemartics. Clean up monitor
2020-04-18 DOR: Added initialization and self-test code.
2020-04-18 DOR: fixed bug on LCD library.
2020-04-18 First layout of Monitor
2020-04-19 Not needed
2020-04-19 Added word working files
2020-04-19 Updated Monitor Schematic
2020-04-19 DOR: updated documentation
2020-04-19 DOR: fixed bugs.
2020-04-20 Update in the PCB design. New docs and images
2020-04-21 First placement of board
2020-04-21 DOR: tmp
2020-04-21 DOR: file moves.
2020-04-21 DOR: WIP. Added I2C communication with monitor, and updated menus to support volume control.
2020-04-21 DOR: added mux function to correctly capture monitor errors.
2020-04-21 Update Schematic documentation
2020-04-21 Removed build files
2020-04-21 DOR: checked correct operation of new menus.
2020-04-22 DOR: added hex file result
2020-04-22 DOR: added binary compile results
2020-04-22 Update in PCB: Schematic and Layout
2020-04-24 New PCB version; I2C Slave works
2020-04-24 WIP, added Quanta measurement, volume overshoot. Fixed volume settings and operation.
2020-04-25 DOR: removed compiled files
2020-04-25 DOR: WIP added power-off, reorganized information display. Added independent overshoot control during inspiration.
2020-04-25 New V1 placement done. Speed up Monitor to 64 MHz
2020-04-26 DOR: WIP added saturation to pressure quanta to avoid deathlock if pquanta goes too high (which would avoid subsequent actuations, and value would not be updated).
2020-04-26 DOR: WIP, added also limit for volume quanta.
2020-04-26 Version 1 of THT PCB
2020-04-26 DOR: Test PWM control of sv2.
2020-04-27 Updated PCB
2020-04-27 DOR: WIP initialization changed.
2020-04-28 Updated PCB with extra Valve
2020-04-28 DOR: fixed initialization routine.
2020-04-29 DOR: added pmax setting also in pressure mode. Optimized ip phase control to avoid oscillations.
2020-05-01 DOR: Added volume-controller pressure mode for more stability.
2020-05-03 First stable version
2020-05-03 Added . in gitignore
2020-05-05 DOR: improved control of two SV2 valves.
2020-05-06 preTest with Artificial doctor
2020-05-07 DOR: added mechanical parts. Dampener not used currently
2020-05-07 DOR: added valve and pressure regulator holders. Used in the prototype
2020-05-09 DOR: fixed several bugs. Switched back to use averaged pressure to partially compensate problems caused by the pressure wave during valve opening.
2020-05-10 First tests with artificial lung. 70 cases. New PCB THT fixing mounting issues
2020-05-11 Update THT board reducing to class 3
2020-05-11 Fixed SilkScreen V1.2 THT
2020-05-11 New SMD PCB
2020-05-11 DOR: changed max volume to 1500ml.
2020-05-12 DOR: added measurement of sv2 valve close to avoid full flow when switching from med to low flow. Optimized control operation to avoid wrong overshoot check at end of inspiration.
2020-05-13 DOR: improved switch between different SV2 flows with highly resistive lung.
2020-05-14 DOR: Refactoring. Added display test showing a sequence of 0 to 9 to check all digits
2020-05-16 Released version of SMD PCB
2020-05-16 Fixed bug in Alarm Very High Pressure. Clean up static definition of variables
2020-05-17 DOR: Code speed optimization by removing all possible divisions.
2020-05-17 DOR: refactoring
2020-05-17 DOR: Refactoring.
2020-05-17 DOR: Fixed display message.
2020-05-17 DOR: re-enabled debug.
2020-05-17 Fixed power off
2020-05-21 DOR: updated minor changes for animal testing.
2020-05-22 Add Alarm SV1 control Disable option
2020-05-22 Change PIN IO Allocation for SMD 1_1 board. New Assembly information version
2020-05-24 DOR: ported lcd to 4-bit parallel. Managed through interrupts.
2020-05-26 DOR: added new version with 6mm hole and taper ends
2020-05-27 DOR: Changed respirator name
2020-05-27 DOR: fixed error report message.
2020-05-27 DOR: added UPF day 2 results
2020-05-28 DOR: added extra engineering menu, to show valve stats, lung stats, and allow Breath detect trigger to be programmed.
2020-05-28 DOR: fixed error in flow rate calculation
2020-05-30 DOR: added 1 extra second to expiration cycle during spontaneous detected breaths. Changed hold IP to compensate for leaks also in Volume control mode by detecting pressure loss with respect to the p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
2020-05-30 DOR: unified pressure leak compensation during inspiration.
2020-05-31 DOR: added extra comparison to the theoretical plateau pressure, to make leak compensation more conservative.
2020-06-01 New SMD PCB version
2020-06-01 Version for SMD 1.2: Added 5V monitor. MIC in CMP1
2020-06-01 Review QFN footprint
2020-06-03 Added MIC functionality. To be tested
2020-06-11 Added GPLv2 license
2020-06-16 First MIC version working
2020-06-17 DOR: changed program default value, added buzzer test at init, added smart default values for IP/MAXV when changing from pressure to volume control and the other way around.
2020-06-17 DOR: changed frequency source used for volume calculation, for increased precision.
2020-06-17 Controller Buzzer detection working I2C disable/enable does not work to send NACK. It does not recover.
2020-06-18 DOR: made configuration more robust, avoiding forbidden configurations.
2020-06-22 Preparing v1_0 release
2020-06-22 DOR: exchanged position of SV2 and SV2bis to comply with latest SMD schematic.
2020-07-08 DOR: minor changes to improve operation in corner conditions. Updated headers
2020-07-08 New version of PCB with two footprints for MPXV5004 and s other small changes
2020-07-08 Updated Assembly instructions
2020-07-08 Version 1.1: Fixed Volume meassure problems
2020-07-08 Hex file for V1_1
2020-07-09 Alarm of EP based on the same value than display. Mean of last 250 ms and full period
2020-07-09 DOR: minor changes to stabilize PEEP
2020-07-09 Rewrite version v1.0 - Removed version v1.1
